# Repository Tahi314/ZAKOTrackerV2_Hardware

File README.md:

# ZAKOTrackerV2 - Hardware

自作VRモーショントラッカー「ZAKOTracker」V2の基板設計データ。

BNO055 IMUの値をESP-NOWで送信するセンサーノード基板です。

## 関連リポジトリ

- [ZAKOTrackerV2_ESP8266](https://github.com/Tahi314/ZAKOTrackerV2_ESP8266) - 送信側ファームウェア（ESP8266）
- [ZAKOTrackerV2_ESP32](https://github.com/Tahi314/ZAKOTrackerV2_ESP32) - 受信側ファームウェア（ESP32）

## 設計環境

- KiCad 6.0

## ディレクトリ構成

- `kicad/` - KiCad プロジェクトファイル
- `3d/` - 3Dモデル
- `pic/` - 画像

## 参考

- [ZAKOTrackerV1.0の解説記事（Zenn）](https://zenn.dev/tahi_314/articles/8bd749271e5c29)

## 著者

- [X](https://x.com/Tahi_314_main)
- [GitHub](https://github.com/Tahi314)

## ライセンス

<br />この作品は<a rel="license" href="http://creativecommons.org/licenses/by-nc/4.0/">クリエイティブ・コモンズ 表示 - 非営利 4.0 国際 ライセンス</a>の下に提供されています。

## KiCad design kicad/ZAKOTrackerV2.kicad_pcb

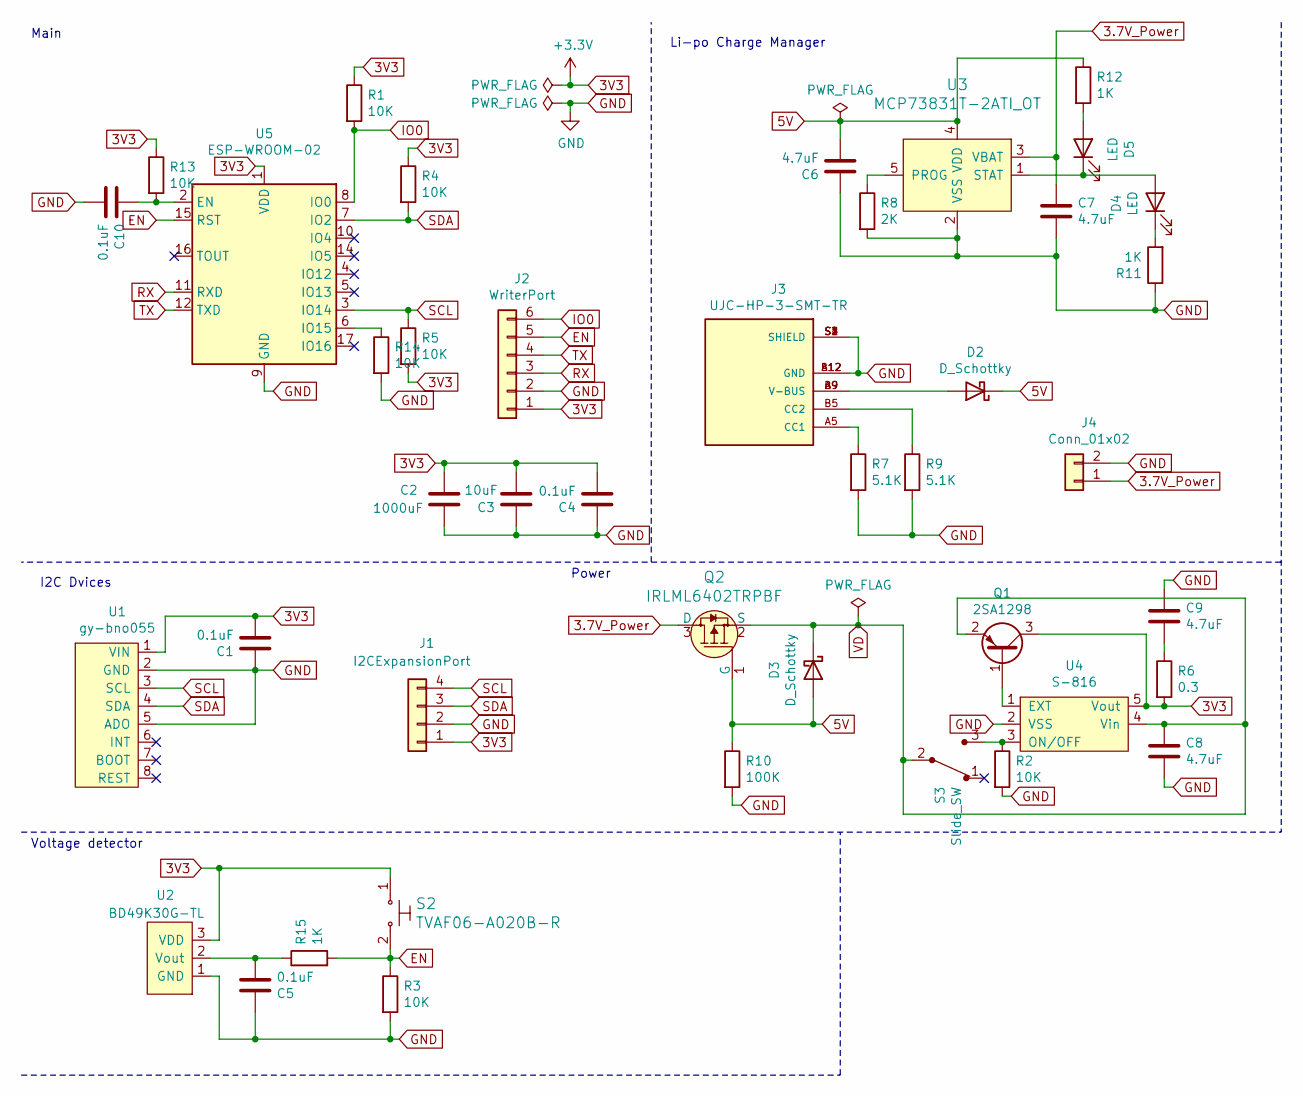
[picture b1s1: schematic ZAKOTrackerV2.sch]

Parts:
C1, C4, C5, C10: 0.1uF; C_0805_2012Metric_Pad1.18x1.45mm_HandSolder
C2: 1000uF; CP_Radial_D8.0mm_P3.50mm
C3: 10uF; C_0805_2012Metric_Pad1.18x1.45mm_HandSolder
C6, C7, C8, C9: 4.7uF; C_0805_2012Metric_Pad1.18x1.45mm_HandSolder
D2, D3: D_Schottky; D_SOD-323_HandSoldering
D4, D5: LED; D_0603_1608Metric_Pad1.05x0.95mm_HandSolder
J1: I2CExpansionPort; JST_XH_B4B-XH-A_1x04_P2.50mm_Vertical
J2: WriterPort; PinHeader_1x06_P2.54mm_Vertical
J3: UJC-HP-3-SMT-TR; CUI_UJC-HP-3-SMT-TR; PARTREV 1.0
J4: Conn_01x02; JST_XH_S2B-XH-A_1x02_P2.50mm_Horizontal
Q1: 2SA1298; SOT-23_Handsoldering
Q2: IRLML6402TRPBF; SOT-23_Handsoldering; MPN IRLML6402TRPBF; Digi-Key_PN IRLML6402PBFCT-ND
R1, R2, R3, R4, R5, R13, R14: 10K; R_0805_2012Metric_Pad1.20x1.40mm_HandSolder
R6: 0.3; R_0805_2012Metric_Pad1.20x1.40mm_HandSolder
R7, R9: 5.1K; R_0805_2012Metric_Pad1.20x1.40mm_HandSolder
R8: 2K; R_0805_2012Metric_Pad1.20x1.40mm_HandSolder
R10: 100K; R_0805_2012Metric_Pad1.20x1.40mm_HandSolder
R11, R12, R15: 1K; R_0805_2012Metric_Pad1.20x1.40mm_HandSolder
S2: TVAF06-A020B-R; MPN B3U-1000P; Digi-Key_PN SW1020CT-ND
S3: Slide_SW; SS-12D01G3; MPN EG1218; Digi-Key_PN EG1903-ND
U1: gy-bno055; gy-bno055-s
U2: BD49K30G-TL; SOT-23-3
U3: MCP73831T-2ATI_OT; SOT-23-5_HandSoldering; MPN MCP73831T-2ATI/OT; Digi-Key_PN MCP73831T-2ATI/OTCT-ND
U4: S-816; SOT-23-5_HandSoldering
U5: ESP-WROOM-02

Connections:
3.7V_Power: C7.1, J4.1, Q2.3 (D), U3.3 (VBAT)
3V3: C1.2, C2.1, C3.2, C4.2, J1.1, J2.1, Q1.3 (C), R1.1, R4.1, R5.2, R6.2, R13.1, S2.1, U1.1 (VIN), U2.3 (VDD), U4.5 (Vout), U5.1 (VDD)
5V: C6.2, D2.1 (K), D3.2 (A), Q2.1 (G), R10.1, R12.1, U3.4 (VDD)
EN: J2.5, R3.1, R15.2, S2.2, U5.15 (RST)
GND: C1.1, C2.2, C3.1, C4.1, C5.1, C6.1, C7.2, C8.2, C9.1, C10.2, J1.2, J2.2, J3.A12 (GND), J3.B12 (GND), J3.S1 (SHIELD), J3.S2 (SHIELD), J3.S3 (SHIELD), J3.S4 (SHIELD), J4.2, R2.2, R3.2, R7.2, R8.2, R9.2, R10.2, R11.1, R14.2, U1.2 (GND), U1.5 (ADO), U2.1 (GND), U3.2 (VSS), U4.2 (VSS), U5.9 (GND), U5.13 (GND), U5.18 (GND), U5.19 (GND)
IO0: J2.6, R1.2, U5.8 (IO0)
unnamed: C5.2, R15.1, U2.2 (Vout)
unnamed: C9.2, R6.1
unnamed: C10.1, R13.2, U5.2 (EN)
unnamed: D2.2 (A), J3.A9 (V-BUS), J3.B9 (V-BUS)
unnamed: D4.1 (K), R11.2
unnamed: D4.2 (A), D5.1 (K), U3.1 (STAT)
unnamed: D5.2 (A), R12.2
unnamed: J3.A5 (CC1), R7.1
unnamed: J3.B5 (CC2), R9.1
unnamed: Q1.1 (B), U4.1 (EXT)
unnamed: R2.1, S3.3, U4.3 (ON/OFF)
unnamed: R8.1, U3.5 (PROG)
unnamed: R14.1, U5.6 (IO15)
RX: J2.3, U5.11 (RXD)
SCL: J1.4, R5.1, U1.3 (SCL), U5.3 (IO14)
SDA: J1.3, R4.2, U1.4 (SDA), U5.7 (IO2)
TX: J2.4, U5.12 (TXD)
VD: C8.1, D3.1 (K), Q1.2 (E), Q2.2 (S), S3.2, U4.4 (Vin)

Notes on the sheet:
I2C Dvices
Main
Power
Voltage detector
Li-po Charge Manager

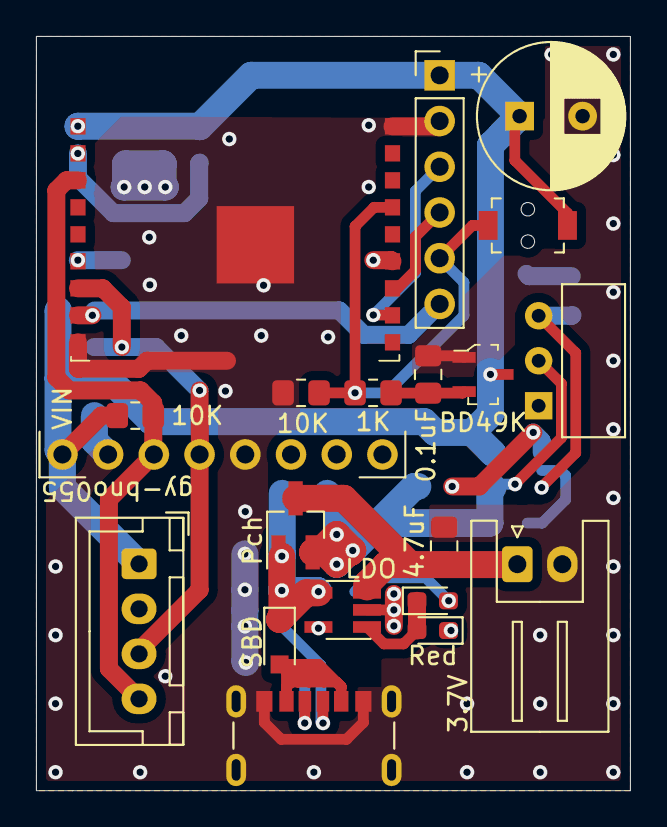
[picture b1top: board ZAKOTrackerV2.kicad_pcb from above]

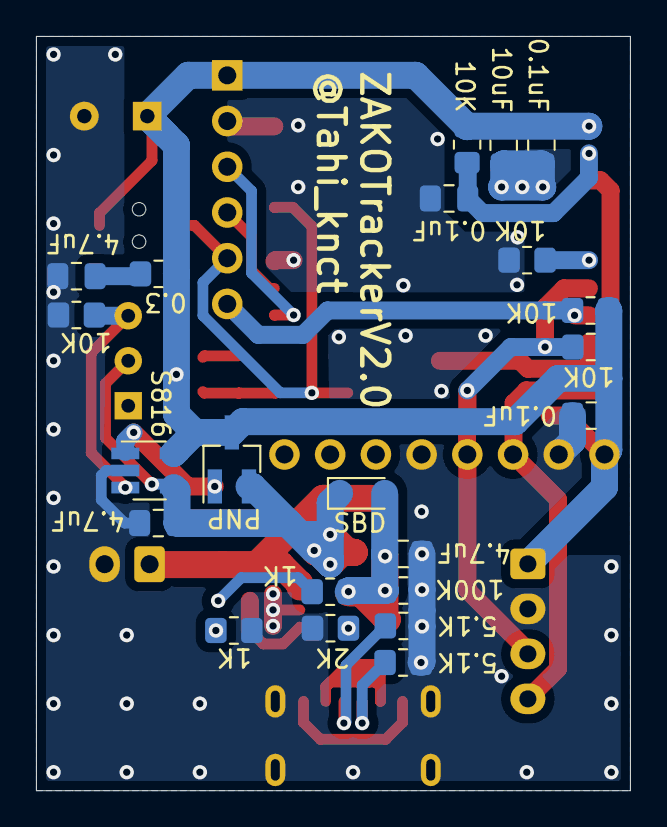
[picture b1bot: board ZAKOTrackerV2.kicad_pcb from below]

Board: 2 copper layers, 33.0 x 41.9 mm, 42 parts (22 on the bottom side), 24 nets.

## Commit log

2022-02-24 add CC licence
2022-02-24 add LICENCE.md
2022-02-24 re add LICENCE.md
2026-03-14 Update README and fix links

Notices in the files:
README.md:
CC BY-NC 4.0
